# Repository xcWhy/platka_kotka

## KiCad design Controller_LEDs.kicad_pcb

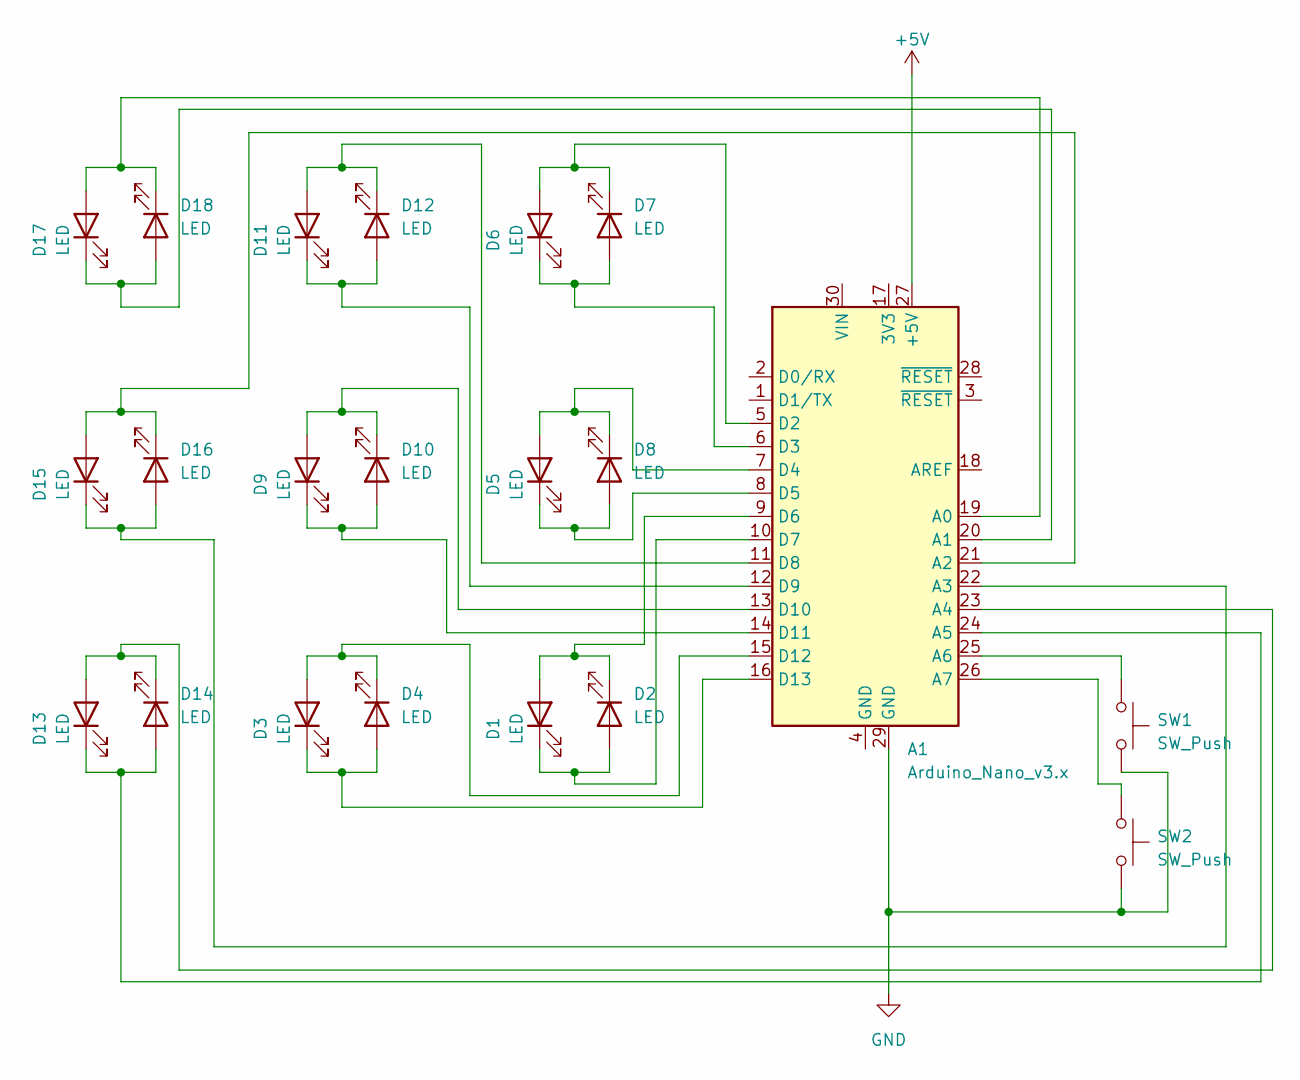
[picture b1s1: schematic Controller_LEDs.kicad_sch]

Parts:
A1: Arduino_Nano_v3.x; Arduino_Nano
D1, D2, D3, D4, D5, D6, D7, D8, D9, D10, D11, D12, D13, D14, D15, D16, D17, D18: LED; LED_D5.0mm
SW1, SW2: SW_Push; SW_TH_Tactile_Omron_B3F-10xx

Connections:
+5V: A1.27 (+5V)
GND: A1.29 (GND), SW1.2, SW2.2
unnamed: A1.19 (A0), D17.2 (A), D18.1 (K)
unnamed: A1.20 (A1), D17.1 (K), D18.2 (A)
unnamed: A1.21 (A2), D15.2 (A), D16.1 (K)
unnamed: A1.22 (A3), D15.1 (K), D16.2 (A)
unnamed: A1.23 (A4), D13.2 (A), D14.1 (K)
unnamed: A1.24 (A5), D13.1 (K), D14.2 (A)
unnamed: A1.25 (A6), SW1.1
unnamed: A1.26 (A7), SW2.1
unnamed: A1.5 (D2), D6.2 (A), D7.1 (K)
unnamed: A1.6 (D3), D6.1 (K), D7.2 (A)
unnamed: A1.7 (D4), D5.2 (A), D8.1 (K)
unnamed: A1.8 (D5), D5.1 (K), D8.2 (A)
unnamed: A1.9 (D6), D1.2 (A), D2.1 (K)
unnamed: A1.10 (D7), D1.1 (K), D2.2 (A)
unnamed: A1.11 (D8), D11.2 (A), D12.1 (K)
unnamed: A1.12 (D9), D11.1 (K), D12.2 (A)
unnamed: A1.13 (D10), D9.2 (A), D10.1 (K)
unnamed: A1.14 (D11), D9.1 (K), D10.2 (A)
unnamed: A1.15 (D12), D3.2 (A), D4.1 (K)
unnamed: A1.16 (D13), D3.1 (K), D4.2 (A)

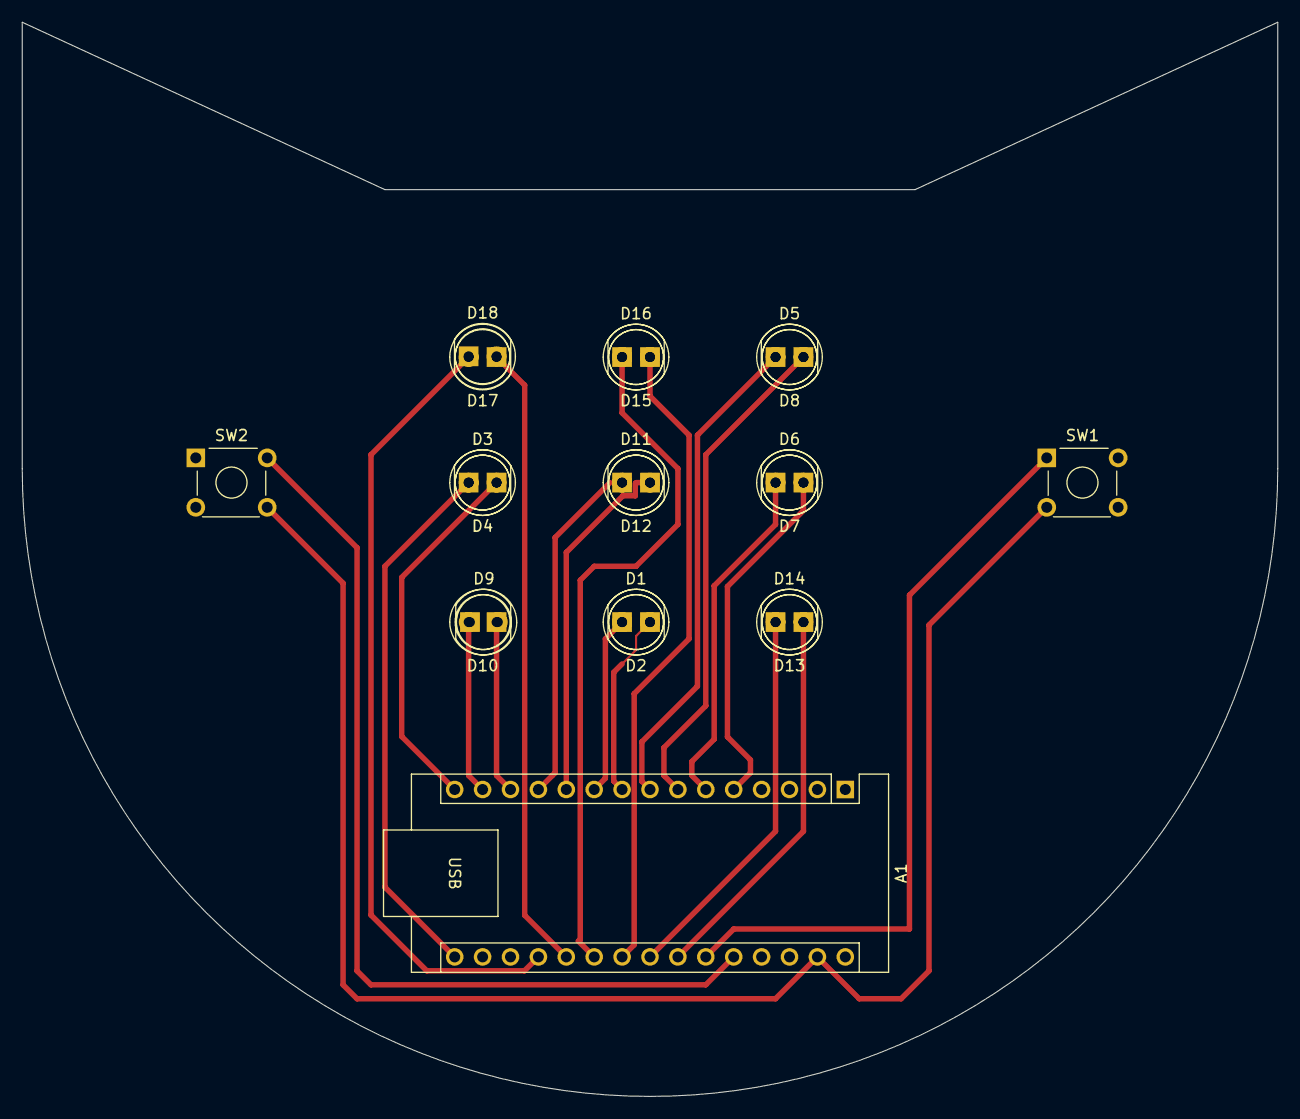
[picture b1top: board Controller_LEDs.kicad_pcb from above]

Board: 2 copper layers, 114.3 x 97.8 mm, 21 parts (0 on the bottom side), 21 nets.
